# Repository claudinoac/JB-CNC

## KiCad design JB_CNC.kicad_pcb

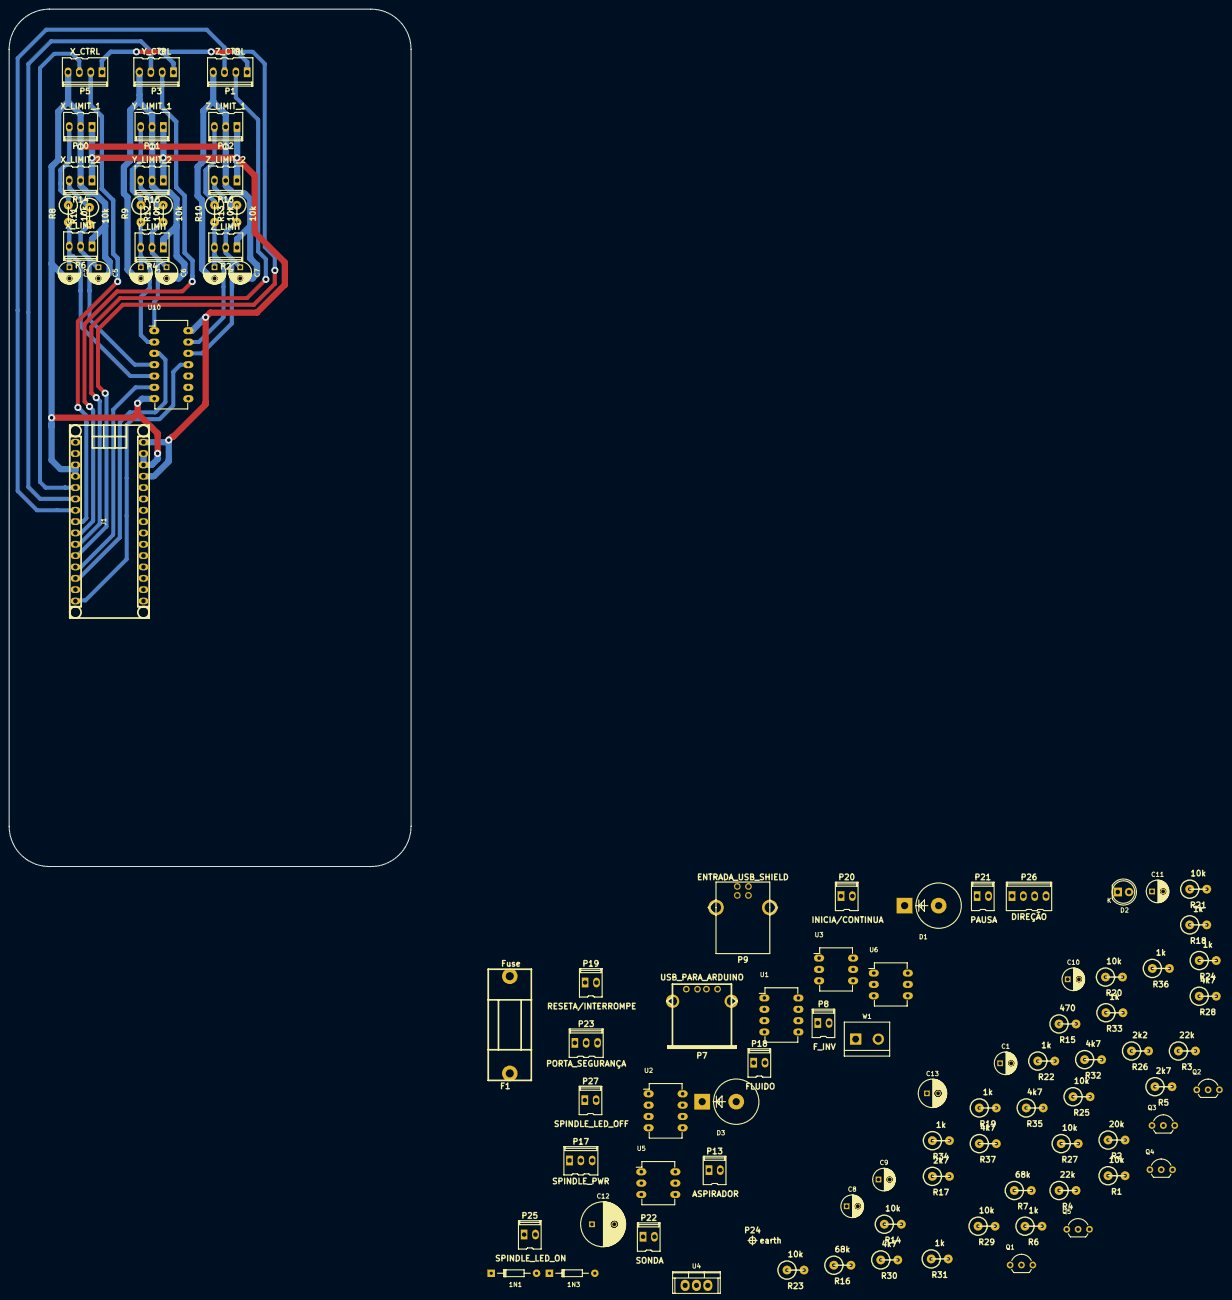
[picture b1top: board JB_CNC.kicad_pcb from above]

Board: 2 copper layers, 90.0 x 192.0 mm, 97 parts (0 on the bottom side), 67 nets.

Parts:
1N1, 1N3: 1N4001; Diode_DO-35_SOD27_Horizontal_RM10
C1, C2, C3, C4, C5, C6, C7, C8, C9, C10, C11: 1uF; C_Radial_D5_L11_P2.5
C12: 100u; C_Radial_D10_L13_P5
C13: 10u; C_Radial_D6.3_L11.2_P2.5
D1: 1N5401; Diode_P600_Vertical_KathodeUp
D2: LED_PWR; LED-5MM
D3: 1K5E68A; Diode_P600_Vertical_KathodeUp
F1: Fuse; fuse_holder_CQ-2
J1: Arduino_Nano_Header; arduino_nano_header
P1: Z_CTRL; kk100_22-23-2041
P2: Z_LIMIT; kk100_22-23-2031
P3: Y_CTRL; kk100_22-23-2041
P4: Y_LIMIT; kk100_22-23-2031
P5: X_CTRL; kk100_22-23-2041
P6: X_LIMIT; kk100_22-23-2031
P7: USB_PARA_ARDUINO; conn_usb_A
P8: F_INV; kk100_22-23-2021
P9: ENTRADA_USB_SHIELD; conn_usb_B
P10: X_LIMIT_1; kk100_22-23-2031
P11: Y_LIMIT_1; kk100_22-23-2031
P12: Z_LIMIT_1; kk100_22-23-2031
P13: ASPIRADOR; kk100_22-23-2021
P14: X_LIMIT_2; kk100_22-23-2031
P15: Y_LIMIT_2; kk100_22-23-2031
P16: Z_LIMIT_2; kk100_22-23-2031
P17: SPINDLE_PWR; kk100_22-23-2031
P18: FLUIDO; kk100_22-23-2021
P19: RESETA/INTERROMPE; kk100_22-23-2021
P20: INICIA/CONTINUA; kk100_22-23-2021
P21: PAUSA; kk100_22-23-2021
P22: SONDA; kk100_22-23-2021
P23: PORTA_SEGURANÇA; kk100_22-23-2031
P24: earth; hole_1mm
P25: SPINDLE_LED_ON; kk100_22-23-2021
P26: DIREÇÃO; kk100_22-23-2041
P27: SPINDLE_LED_OFF; kk100_22-23-2021
Q1, Q2, Q3, Q4, Q5: BC546; TO-92_Inline_Wide
R1, R8, R9, R10, R11, R12, R13, R14, R20, R21, R23, R25, R27, R29: 10k; rc07_vert
R2: 20k; rc07_vert
R3, R4: 22k; rc07_vert
R5, R17: 2k7; rc07_vert
R6, R18, R19, R22, R24, R31, R33, R34, R36: 1k; rc07_vert
R7, R16: 68k; rc07_vert
R15: 470; rc07_vert
R26: 2k2; rc07_vert
R28, R30, R32, R35, R37: 4k7; rc07_vert
U1, U2: CA3140; DIP-8_W7.62mm_LongPads
U3, U5, U6: 4N25; DIP-6_W7.62mm_LongPads
U4: LM7805CT; TO-220
U10: 74LS32; DIP-14_W7.62mm_LongPads
W1: FONTE; bornier2

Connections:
+5V: C13.1, J1.27, J1.30, P7.1, P10.1, P11.1, P12.1, P14.1, P15.1, P16.1, P19.1, P20.1, P21.1, R6.2, R16.1, R30.2, R31.1, R33.2, R36.2, U4.3, U10.14
+14.2V: 1N1.1, 1N3.1, C12.1, D1.1, D2.2, D3.1, P13.1, P18.1, R7.1, U1.7, U2.7, U4.1
/+24V(EXT): P17.1, P26.2, R28.1, R35.2, R37.1
/CCW/STOP: P26.3, R37.2, U5.5
/COOLANT_EN: J1.22, R17.2
/CW/STOP: P26.1, R35.1, U6.5
/FEED_HOLD*: C11.1, J1.20, R25.1
/GND(EXT): P17.3, P26.4, U3.4, U5.4, U6.4
/LIG/DESL: P17.2, R28.2, U3.5
/PROBE*: C10.1, J1.24, R23.1
/RESET/ABORT*: C8.1, J1.19, R20.1
/SAFETY_IN: P21.2, P23.1, R24.2
/SPINDLE_DIR: J1.16, R29.2
/SPINDLE_EN: R5.2, R15.2, R27.1, U3.1
/SPINDLE_PWM: J1.14, R1.1
/START/RESUME*: C9.1, J1.21, R21.1
/STEPPER_EN: J1.11, P1.1, P3.1, P5.1
/V_CTRL: C1.1, R1.2, U1.3, U2.3
/X_DIR: J1.8, P5.2
/X_LIMIT*: J1.12, U10.6
/X_LIMIT_A: C2.1, P6.3, R8.2, U10.5
/X_LIMIT_B: C5.1, P6.2, R11.2, U10.4
/X_STEP: J1.5, P5.3
/Y_DIR: J1.9, P3.2
/Y_LIMIT*: J1.13, U10.3
/Y_LIMIT_A: C3.1, P4.3, R9.2, U10.2
/Y_LIMIT_B: C6.1, P4.2, R12.2, U10.1
/Y_STEP: J1.6, P3.3
/Z_DIR: J1.10, P1.2
/Z_LIMIT*: J1.15, U10.11
/Z_LIMIT_A: C4.1, P2.3, R10.2, U10.13
/Z_LIMIT_B: C7.1, P2.2, R13.2, U10.12
/Z_STEP: J1.7, P1.3
GND: C1.2, C2.2, C3.2, C4.2, C5.2, C6.2, C7.2, C8.2, C9.2, C10.2, C11.2, C12.2, C13.2, D3.2, J1.3, J1.4, J1.28, J1.29, P1.4, P2.1, P3.4, P4.1, P5.4, P6.1, P7.4, P8.2, P9.4, P10.2, P11.2, P12.2, P14.2, P15.2, P16.2, P22.1, P23.2, P24.1, P27.2, Q1.3, Q2.3, Q3.3, Q4.3, Q5.3, R2.1, R4.2, R18.1, R19.1, R22.2, R24.1, R26.2, U1.4, U2.4, U3.2, U4.2, U6.2, U10.7, W1.1
unnamed: 1N1.2, P13.2, Q1.1
unnamed: 1N3.2, P18.2, Q3.1
unnamed: D1.2, F1.1
unnamed: D2.1, R26.1
unnamed: F1.2, W1.2
unnamed: P7.2, P9.2
unnamed: P7.3, P9.3
unnamed: P8.1, R3.2, U1.6
unnamed: P9.1, R4.1
unnamed: P10.3, R8.1
unnamed: P11.3, R9.1
unnamed: P12.3, R10.1
unnamed: P14.3, R11.1
unnamed: P15.3, R12.1
unnamed: P16.3, R13.1
unnamed: P19.2, R18.2, R20.2
unnamed: P20.2, R19.2, R21.2
unnamed: P22.2, R22.1, R23.2
unnamed: P23.3, R25.2
unnamed: P25.1, R30.1
unnamed: P25.2, Q5.1, R31.2, R32.2
unnamed: P27.1, R32.1
unnamed: Q1.2, R5.1, R7.2
unnamed: Q2.1, R6.1, R15.1
unnamed: Q2.2, R14.1, R16.2
unnamed: Q3.2, R17.1
unnamed: Q4.1, R33.1, R34.2, U5.2
unnamed: Q4.2, R29.1
unnamed: Q5.2, R27.2
unnamed: R2.2, R3.1, U1.2
unnamed: R14.2, U2.2, U2.6
unnamed: R34.1, U6.1
unnamed: R36.1, U5.1

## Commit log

2016-11-04 V_0.9
2016-11-04 Versão 0.9 UNO
2016-11-04 Desenho da placa em andamento
2016-11-05 primeiro commit colaborativo
2016-11-05 Mudei o pad
2016-11-08 Trilhas finalizadas
2016-11-09 Consertado erro de Esquema + Netlist
2016-12-08 modificações acerca do probe
2016-12-22 Filtros Reprojetados
2017-01-16 Reorganização
2017-01-16 Removidos arquivos desnecessários
2017-01-16 Adicionado arquivos essenciais
2017-01-16 removido libraries desnecessários
2017-01-16 Removidos arquivos desnecessários e adicionado G-codes e Gerbers
2017-01-16 adicionado library backup
2017-01-18 Modificado módulo SPINDLE
2017-01-23 Refeitos circuitos de acionamento do SPINDLE, ASPIRADOR e BOMBA
2017-01-24 Finalizado Esquema V0.2
2017-01-24 Circuito Redesenhado
2017-01-30 Adicionado Fusível
2017-01-30 Desenho parcial da placa
